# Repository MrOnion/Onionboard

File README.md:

# Onionboard PCB for FreeEMS

This PCB is intended to be used in conjunction with a separate microcontroller module to create a basic engine management system. It has a simple power supply and enough general purpose I/O to get started. Basically any microcontroller and software combo can be used but it is particulary designed to be used with the open-source FreeEMS project.

http://freeems.org/

Its ideal for people who wants to experiment and learn about the world of engine management.

The project is done with CadSoft Eagle version 6.x and is kept within the freeware limitations.

http://www.cadsoftusa.com/download-eagle/freeware/

## Features

* 2-Layer PCB
* Size is about 10x10cm (fits in a euro case)
* 5V LDO regulated power supply with VDR protection
* 2 Polyfuse protected 5V reference voltage outputs
* 4 auto-protected injector outputs (high impedance only)
* 2 auto-protected accessory outputs
* 4 mosfet drivers for ignition amplifiers (5V or 12V)
* 4 protected A/D inputs
* 4 protected temperature inputs (can be used as normal A/D)
* 2 protected on/off switch inputs
* 2 ground loop monitor inputs
* CEL LED and run/load switch for FreeEMS

One thing to point out is that at this stage the board DOES NOT have VR/Hall sensor inputs. As these sensors are mandatory to operate an EMS there are pin headers/DIP8 socket and places for shunt resistors (used with VR) to be used with a separate BrickRPM VR conditioner board. More info at: http://brickems.com/brickrpm/

## Notes

The schematic and board file both have a placeholder for git commit id. This is used with the git clean/smudge filter. The .gitattributes file is included with the project but it only defines the files to be filtered with a filter called "hasher". You can use this feature by adding this into your .git/config file:
```
[filter "hasher"]
        smudge = sed \"s/GIT %GIT_COMMIT_ID%/GIT `git rev-parse --verify HEAD --short`/\"
        clean = sed \"s/GIT [0-9a-z]\\{7\\}/GIT %GIT_COMMIT_ID%/\"
```
As you can see this is OS specific and works straight in Linux and OSX.

The filter has one downside which is the need to make an extra deletion and checkout for the id to be "smudged". For example if you clone this project the git placeholder don't have the current id. You need to delete the files and checkout them for the id to be updated:

```
$ rm onionboard.sch onionboard.brd 
$ git checkout onionboard.sch onionboard.brd
```

The project uses a separate Molex connector library I found here:
https://code.google.com/p/rdubniewski-test/source/browse/trunk/eagle.lib/con-molex-5569.lbr
It's also included in the libs directory.

If you decide to home etch this pcb I recommend to make the vias larger (the copper area) before doing so. This way its easier to drill them and solder the connecting wire.

Heres a good tip for home made vias:
http://www.youritronics.com/double-layer-pcb-home-made-vias/

## TODO

* Get more testing done and lots of driving/racing.
* Possibly put a dual VR conditioner on board (MAX992x based)
* Also one H-bridge driver would be ideal

## CPU Modules used with FreeEMS (MC9S12XDP512)

* **TA Adapt9S12XDP512** - http://www.technologicalarts.ca/shop/store/details/453/11/microcontrollers/adapt9s12xdp512m2-xgate-mcu-module,-full-configuration.html
* **ElMicro CardS12** - http://elmicro.com/en/cards12.html
* **WayEngineer MC9S12XDP512-core** - http://www.wayengineer.com/index.php?main_page=product_info&products_id=281

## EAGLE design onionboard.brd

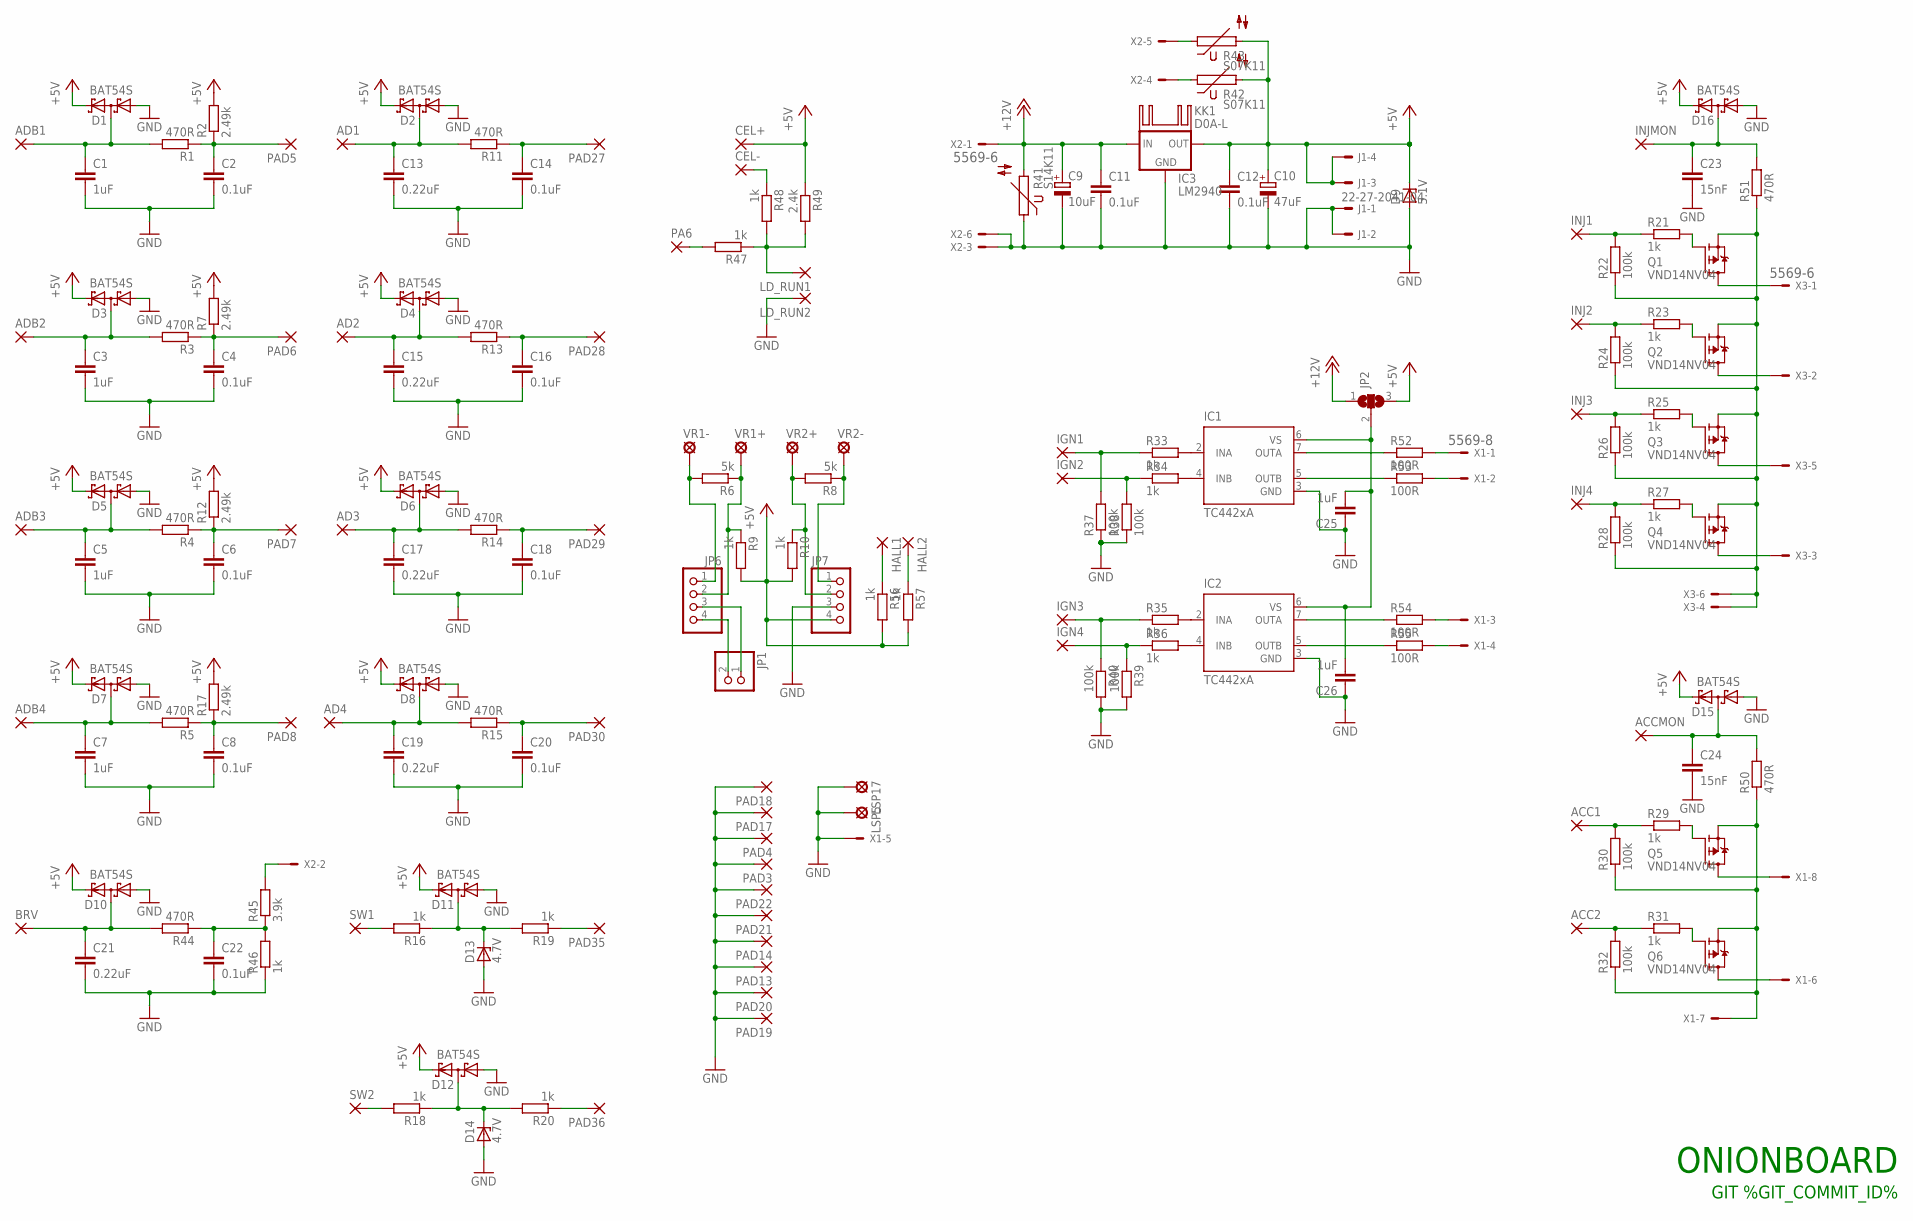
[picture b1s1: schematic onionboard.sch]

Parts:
ACC1, ACC2: SMD2; SMD1,27-2,54
ACCMON: SMD2; SMD1,27-2,54
AD1, AD2, AD3, AD4: SMD2; SMD1,27-2,54
ADB1, ADB2, ADB3, ADB4: SMD2; SMD1,27-2,54
BRV: SMD2; SMD1,27-2,54
C1, C3, C5, C7: 1uF; C0805
C2, C4, C6, C8, C14, C16, C18, C20, C22: 0.1uF; C0805
C9: 10uF; SMC_E
C10: 47uF; SMC_E
C11, C12: 0.1uF; C1206
C13, C15, C17, C19, C21: 0.22uF; C0805
C23, C24: 15nF; C0805
C25, C26: 1uF; C1206
CEL+: SMD2; SMD1,27-2,54
CEL-: SMD2; SMD1,27-2,54
D1, D2, D3, D4, D5, D6, D7, D8, D10, D11, D12, D15, D16: BAT54S; SOT23
D9: 5.1V; P1Z12
D13, D14: 4.7V; SOT23
HALL1, HALL2: 1,6/0,8
IC1, IC2: TC442xA; SO08
IC3: LM2940; 78XXL
IGN1, IGN2, IGN3, IGN4: SMD2; SMD1,27-2,54
INJ1, INJ2, INJ3, INJ4: SMD2; SMD1,27-2,54
INJMON: SMD2; SMD1,27-2,54
J1: 22-27-2041-04; 6410-04
JP1: PINHD-1X2; 1X02
JP2: SJ2W; SJ_2
JP6, JP7: PINHD-1X4; 1X04
KK1: D0A-L; D02A-L
LD_RUN1, LD_RUN2: SMD2; SMD1,27-2,54
LSP5, LSP17: LSP10
PA6: SMD2; SMD1,27-2,54
PAD3, PAD4, PAD5, PAD6, PAD7, PAD8, PAD13, PAD14, PAD17, PAD18, PAD19, PAD20, PAD21, PAD22, PAD27, PAD28, PAD29, PAD30, PAD35, PAD36: SMD2; SMD1,27-2,54
Q1, Q2, Q3, Q4, Q5, Q6: VND14NV04; TO252
R1, R3, R4, R5, R11, R13, R14, R15, R44, R50, R51: 470R; R1206
R2, R7, R12, R17: 2.49k; M0805
R6, R8: 5k; 0411/15
R9, R10, R56, R57: 1k; R0805
R16, R18, R19, R20: 1k; R1206
R21, R23, R25, R27, R29, R31, R33, R34, R35, R36, R46, R47, R48: 1k; M0805
R22, R24, R26, R28, R30, R32, R37, R38, R39, R40: 100k; M0805
R41: S14K11
R42, R43: S07K11
R45: 3.9k; M0805
R49: 2.4k; M0805
R52, R53, R54, R55: 100R; 0414V
SW1, SW2: SMD2; SMD1,27-2,54
VR1+, VR1-, VR2+, VR2-: LSP10
X1: 5569-8
X2, X3: 5569-6

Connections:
+5V: C10.+, C12.1, CEL+.1, D1.2 (C2), D2.2 (C2), D3.2 (C2), D4.2 (C2), D5.2 (C2), D6.2 (C2), D7.2 (C2), D8.2 (C2), D9.C, D10.2 (C2), D11.2 (C2), D12.2 (C2), D15.2 (C2), D16.2 (C2), IC3.OUT, J1.3, J1.4, JP2.3, JP7.4, R2.2, R7.2, R9.2, R10.2, R12.2, R17.2, R42.2, R43.2, R49.1, R56.2, R57.2
+12V: C9.+, C11.1, IC3.IN, JP2.1, R41.2, X2.1
GND: C1.2, C2.2, C3.2, C4.2, C5.2, C6.2, C7.2, C8.2, C9.-, C10.-, C11.2, C12.2, C13.2, C14.2, C15.2, C16.2, C17.2, C18.2, C19.2, C20.2, C21.2, C22.2, C23.2, C24.2, C25.1, C26.1, D1.1 (A1), D2.1 (A1), D3.1 (A1), D4.1 (A1), D5.1 (A1), D6.1 (A1), D7.1 (A1), D8.1 (A1), D9.A, D10.1 (A1), D11.1 (A1), D12.1 (A1), D13.1 (A), D14.1 (A), D15.1 (A1), D16.1 (A1), IC1.3 (GND), IC2.3 (GND), IC3.GND, J1.1, J1.2, JP7.3, LD_RUN2.1, LSP5.MP, LSP17.MP, PAD3.1, PAD4.1, PAD13.1, PAD14.1, PAD17.1, PAD18.1, PAD19.1, PAD20.1, PAD21.1, PAD22.1, R37.1, R38.1, R39.2, R40.2, R41.1, R46.1, X1.5, X2.3, X2.6
GNDAUX: Q5.2 (S), Q6.2 (S), R30.1, R32.1, R50.1, X1.7
GNDINJ: Q1.2 (S), Q2.2 (S), Q3.2 (S), Q4.2 (S), R22.1, R24.1, R26.1, R28.1, R51.1, X3.4, X3.6
IGNVCC: C25.2, C26.2, IC1.6 (VS), IC2.6 (VS), JP2.2
unnamed: C2.1, PAD5.1, R1.1, R2.1
unnamed: C14.1, PAD27.1, R11.1
unnamed: AD1.1, C13.1, D2.3 (C1A2), R11.2
unnamed: AD2.1, C15.1, D4.3 (C1A2), R13.2
unnamed: C16.1, PAD28.1, R13.1
unnamed: ADB1.1, C1.1, D1.3 (C1A2), R1.2
unnamed: Q6.3 (D), X1.6
unnamed: ADB2.1, C3.1, D3.3 (C1A2), R3.2
unnamed: C4.1, PAD6.1, R3.1, R7.1
unnamed: C18.1, PAD29.1, R14.1
unnamed: AD3.1, C17.1, D6.3 (C1A2), R14.2
unnamed: IGN1.1, R33.1, R37.2
unnamed: AD4.1, C19.1, D8.3 (C1A2), R15.2
unnamed: IGN2.1, R34.1, R38.2
unnamed: C20.1, PAD30.1, R15.1
unnamed: ADB3.1, C5.1, D5.3 (C1A2), R4.2
unnamed: ADB4.1, C7.1, D7.3 (C1A2), R5.2
unnamed: C6.1, PAD7.1, R4.1, R12.1
unnamed: PA6.1, R47.2
unnamed: IGN3.1, R35.1, R40.1
unnamed: IGN4.1, R36.1, R39.1
unnamed: IC1.7 (OUTA), R52.1
unnamed: IC2.5 (OUTB), R55.1
unnamed: C8.1, PAD8.1, R5.1, R17.1
unnamed: JP6.1, R6.2, VR1-.MP
unnamed: IC1.5 (OUTB), R53.1
unnamed: IC2.7 (OUTA), R54.1
unnamed: JP6.2, R6.1, R9.1, VR1+.MP
unnamed: JP7.2, R8.2, R10.1, VR2+.MP
unnamed: JP7.1, R8.1, VR2-.MP
unnamed: ACCMON.1, C24.1, D15.3 (C1A2), R50.2
unnamed: C23.1, D16.3 (C1A2), INJMON.1, R51.2
unnamed: ACC1.1, R29.1, R30.2
unnamed: Q5.3 (D), X1.8
unnamed: INJ1.1, R21.1, R22.2
unnamed: INJ2.1, R23.1, R24.2
unnamed: INJ3.1, R25.1, R26.2
unnamed: INJ4.1, R27.1, R28.2
unnamed: IC1.2 (INA), R33.2
unnamed: IC1.4 (INB), R34.2
unnamed: IC2.4 (INB), R36.2
unnamed: IC2.2 (INA), R35.2
unnamed: R45.2, X2.2
unnamed: JP1.1, JP6.3
unnamed: R52.2, X1.1
unnamed: R43.1, X2.5
unnamed: R42.1, X2.4
unnamed: ACC2.1, R31.1, R32.2
unnamed: R53.2, X1.2
unnamed: R54.2, X1.3
unnamed: JP1.2, JP6.4
unnamed: D11.3 (C1A2), D13.3 (C), R16.1, R19.2
unnamed: PAD36.1, R20.1
unnamed: D12.3 (C1A2), D14.3 (C), R18.1, R20.2
unnamed: Q2.1 (G), R23.2
unnamed: Q3.1 (G), R25.2
unnamed: Q4.1 (G), R27.2
unnamed: Q5.1 (G), R29.2
unnamed: Q6.1 (G), R31.2
unnamed: Q1.1 (G), R21.2
unnamed: BRV.1, C21.1, D10.3 (C1A2), R44.2
unnamed: C22.1, R44.1, R45.1, R46.2
unnamed: R55.2, X1.4
unnamed: HALL2.1, R57.1
unnamed: R16.2, SW1.1
unnamed: PAD35.1, R19.1
unnamed: R18.2, SW2.1
unnamed: HALL1.1, R56.1
unnamed: Q4.3 (D), X3.3
unnamed: LD_RUN1.1, R47.1, R48.2, R49.2
unnamed: Q3.3 (D), X3.5
unnamed: Q2.3 (D), X3.2
unnamed: Q1.3 (D), X3.1
unnamed: CEL-.1, R48.1

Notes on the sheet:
ONIONBOARD
GIT %GIT_COMMIT_ID%

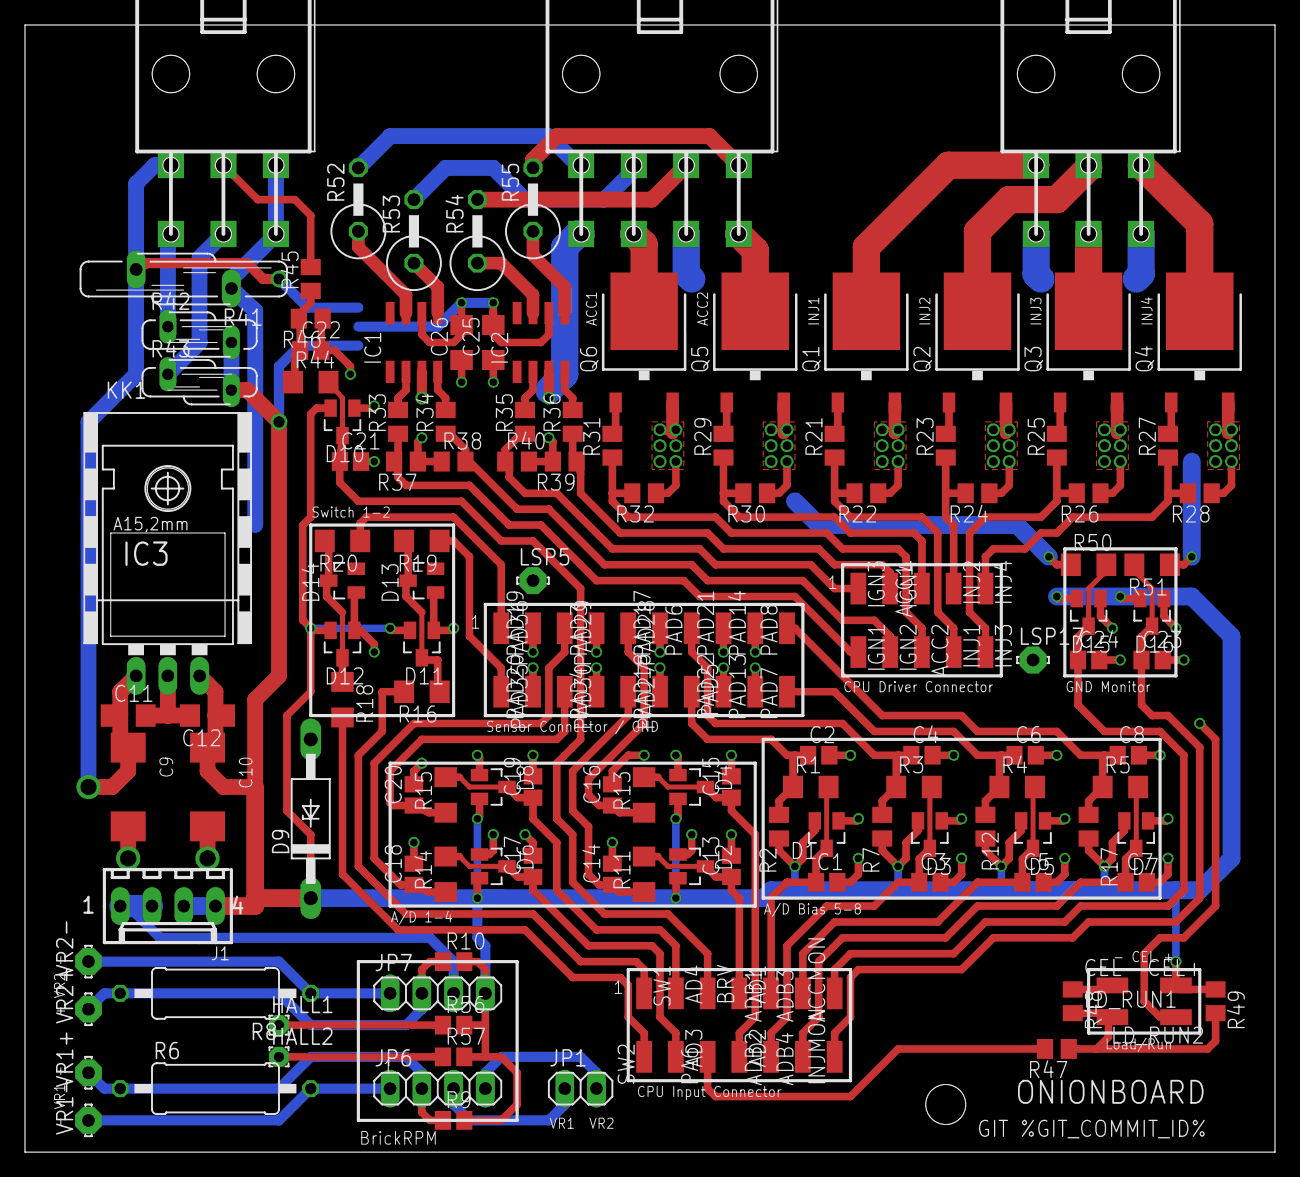
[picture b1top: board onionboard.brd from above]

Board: 4 copper layers, 100.0 x 90.2 mm, 173 parts (1 on the bottom side), 80 nets.

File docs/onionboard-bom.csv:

Qty;Value;Package;Parts;Description
1;;1X02;JP1;Through-hole pin header (VR1/2 Out)
2;;1X04;JP6, JP7;Through-hole pin header (BrickRPM)
48;;SMD1,27-2,54;ACC1, ACC2, ACCMON, AD1, AD2, AD3, AD4, ADB1, ADB2, ADB3, ADB4, BRV, CEL+, CEL-, IGN1, IGN2, IGN3, IGN4, INJ1, INJ2, INJ3, INJ4, INJMON, LD_RUN1, LD_RUN2, PA6, PAD3, PAD4, PAD5, PAD6, PAD7, PAD8, PAD13, PAD14, PAD17, PAD18, PAD19, PAD20, PAD21, PAD22, PAD27, PAD28, PAD29, PAD30, PAD35, PAD36, SW1, SW2;SMD pin headers (pin count)
4;1uF;C0805;C1, C3, C5, C7;CAPACITOR, A/D bias inputs
9;0.1uF;C0805;C2, C4, C6, C8, C14, C16, C18, C20, C22;CAPACITOR, A/D channels
2;0.1uF;C1206;C11, C12;CAPACITOR, Power supply
5;0.22uF;C0805;C13, C15, C17, C19, C21;CAPACITOR, A/D non-biased inputs
2;15nF;C0805;C23, C24;CAPACITOR, GND monitors
2;1uF;C1206;C25, C26;CAPACITOR, MOSFET drivers
1;10uF;SMC_E;C9;POLARIZED CAPACITOR, Power supply
1;47uF;SMC_E;C10;POLARIZED CAPACITOR, Power supply
2;5k;411;R6, R8;RESISTOR, Shunt
4;100R;411;R52, R53, R54, R55;RESISTOR, Current limit
11;470R;R1206;R1, R3, R4, R5, R11, R13, R14, R15, R44, R50, R51;RESISTOR, A/D channels
10;100k;M0805;R22, R24, R26, R28, R30, R32, R37, R38, R39, R40;RESISTOR, Output pulldown
13;1k;M0805;R21, R23, R25, R27, R29, R31, R33, R34, R35, R36, R46, R47, R48;RESISTOR, Output limit, BRV, CEL/Load
4;1k;R0805;R9, R10, R56, R57;RESISTOR, BrickRPM hall mod
4;1k;R1206;R16, R18, R19, R20;RESISTOR, Switch inputs
4;2.49k;M0805;R2, R7, R12, R17;RESISTOR, A/D Bias
1;3.9k;M0805;R45;RESISTOR, BRV
1;2.4k;M0805;R49;RESISTOR, CEL
1;5.1V;P1Z12;D9;Z-Diode, Power supply 
2;4.7V;SOT23;D13, D14;Z-Diode, Switch inputs
13;BAT54S;SOT23;D1, D2, D3, D4, D5, D6, D7, D8, D10, D11, D12, D15, D16;Schottky Diodes, A/D channels
1;22-27-2041-04;6410-04;J1;CONNECTOR Molex, Power supply
2;5569-6;5569-6;X2, X3;4.20mm Pitch Mini-Fit Jr.™ - 6 pin
1;5569-8;5569-8;X1;4.20mm Pitch Mini-Fit Jr.™ - 8 pin
1;D0A-L;D02A-L;KK1;HEATSINK
1;LM2940;78XXL;IC3;VOLTAGE REGULATOR
2;RXE030;RXE030;R42, R43;POLYFUSE, Vref outputs
1;S14K11;S14K11;R41;VARISTOR, Power supply
2;TC442xA;SO08;IC1, IC2;Dual High-Speed Power MOSFET Drivers
6;VND14NV04;TO252 (DPAK);Q1, Q2, Q3, Q4, Q5, Q6;Fully autoprotected Power MOSFET

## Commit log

2013-10-10 Cleaned up and rearranged the schematic. Moved two ground vias on monitor schottkys
2013-10-11 more schematic clean up
2013-10-12 Even more schematic refactor and added values to components. Added silkscreen for molex connectors
2013-10-12 Added git commit id to schematic and added the filter into gitattributes. Also updated README with the commit id filter info
2013-10-26 Changed VDR/MOV size from 20mm to 14mm. Moved powersupply section a bit lower to fit the heatsink properly
2014-02-02 Added BOM and schematic PDF to docs
